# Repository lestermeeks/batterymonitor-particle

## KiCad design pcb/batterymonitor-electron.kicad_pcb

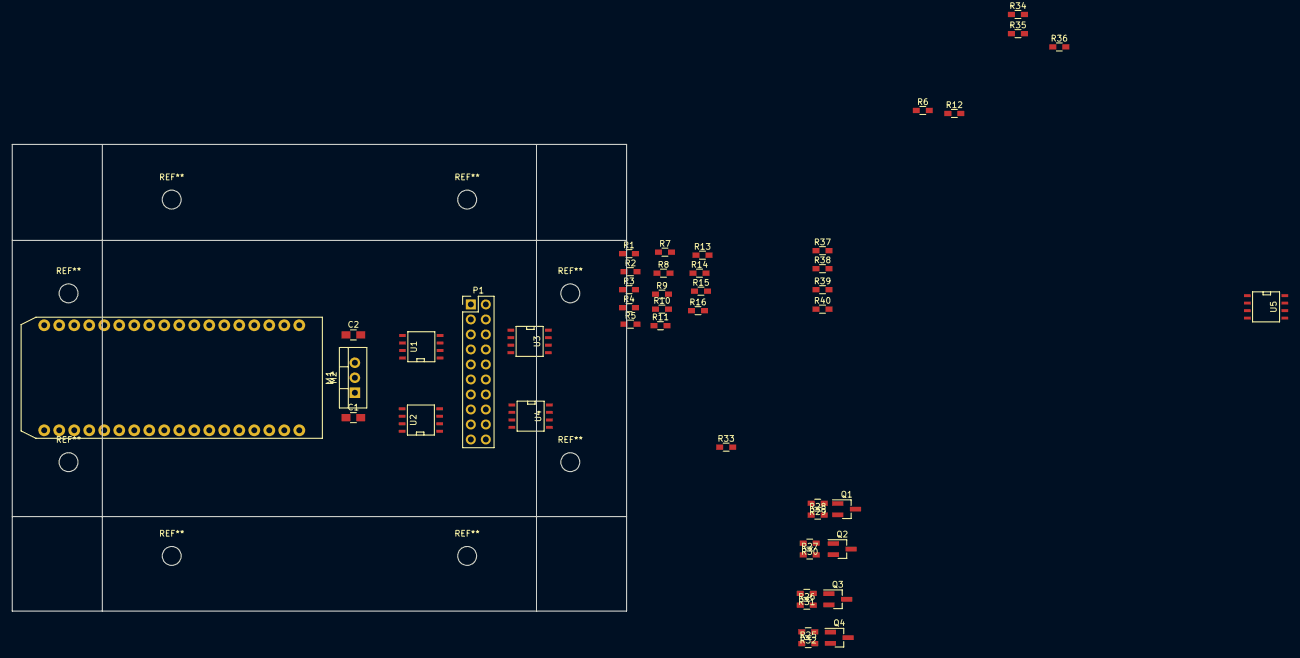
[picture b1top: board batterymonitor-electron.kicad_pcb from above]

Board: 2 copper layers, 104.0 x 79.0 mm, 46 parts (0 on the bottom side), 40 nets, no tracks yet.

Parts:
C1, C2: C_Small; C_0805_HandSoldering
M1: particle_electron
M2: R-78E-0.5; TO-220_Vertical
P1: CONN_02X10; Pin_Header_Straight_2x10_Pitch2.54mm
Q1, Q2, Q3, Q4: Q_NMOS_GSD; SOT-23_Handsoldering
R1, R2, R3, R4: 10K; R_0603_HandSoldering
R5, R6, R7, R8: 0R; R_0603_HandSoldering
R9, R10, R11, R12: 4.75K; R_0603_HandSoldering
R13, R14, R15, R16, R25, R26, R27, R28, R37, R38, R39, R40: 47K; R_0603_HandSoldering
R29, R30, R31, R32, R33, R34, R35, R36: 1K; R_0603_HandSoldering
U1, U2, U3, U4, U5: DA108S1; SOIC-8-N

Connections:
+3V3: M1.36, P1.11, U5.5, U5.6
+5V: C2.1, M1.1, M2.3
+12V: C1.1, M2.1, P1.1, U1.5, U1.6, U2.5, U2.6, U3.5, U3.6, U4.5, U4.6
/12V_IN_0: P1.10, R36.1, R37.1, U3.4
/12V_IN_1: P1.8, R35.1, R38.1, U3.3
/12V_IN_2: P1.6, R34.1, R39.1, U3.2
/12V_IN_3: P1.4, R33.1, R40.1, U3.1
/12V_OUT_0: P1.20, Q4.3, U4.4
/12V_OUT_1: P1.18, Q3.3, U4.3
/12V_OUT_2: P1.16, Q2.3, U4.2
/12V_OUT_3: P1.14, Q1.3, U4.1
/THERM_0: P1.19, R8.2, U2.4
/THERM_1: P1.17, R7.2, U2.3
/THERM_2: P1.15, R6.2, U2.2
/THERM_3: P1.13, R5.2, U2.1
/VSENSE_0: P1.9, R4.2, U1.4
/VSENSE_1: P1.7, R3.2, U1.3
/VSENSE_2: P1.5, R2.2, U1.2
/VSENSE_3: P1.3, R1.2, U1.1
GND: C1.2, C2.2, M1.2, M1.33, M2.2, Q1.2, Q2.2, Q3.2, Q4.2, R9.2, R10.2, R11.2, R12.2, R13.2, R14.2, R15.2, R16.2, R25.2, R26.2, R27.2, R28.2, R37.2, R38.2, R39.2, R40.2, U1.7, U1.8, U2.7, U2.8, U3.7, U3.8, U4.7, U4.8, U5.7, U5.8
unnamed: M1.5, R1.1, R16.1
unnamed: M1.6, R2.1, R15.1
unnamed: M1.7, R3.1, R14.1
unnamed: M1.8, R4.1, R13.1
unnamed: M1.9, R5.1, R12.1
unnamed: M1.10, R6.1, R11.1
unnamed: M1.11, R7.1, R10.1
unnamed: M1.12, R8.1, R9.1
unnamed: M1.25, R36.2, U5.4
unnamed: M1.26, R35.2, U5.3
unnamed: M1.27, R34.2, U5.2
unnamed: M1.28, R33.2, U5.1
unnamed: M1.29, R25.1, R32.2
unnamed: M1.30, R26.1, R31.2
unnamed: M1.31, R27.1, R30.2
unnamed: M1.32, R28.1, R29.2
unnamed: Q1.1, R29.1
unnamed: Q2.1, R30.1
unnamed: Q3.1, R31.1
unnamed: Q4.1, R32.1

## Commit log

2017-03-17 initial pcb concept schematic
2017-03-20 added pcb cuts
